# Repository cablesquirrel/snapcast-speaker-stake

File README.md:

# Snapcast Speaker Stake

Hardware and firmware design to retrofit the [Hampton Bay B0029RA](https://www.homedepot.com/p/Hampton-Bay-16-9-in-Black-Outdoor-Landscape-Speaker-B0029RA-2/305754399) outdoor Bluetooth speaker into a [Snapcast](https://github.com/snapcast/snapcast) client.

The design uses an [ESP32-S3 (Seeed XIAO)](https://www.seeedstudio.com/XIAO-ESP32S3-p-5627.html) along with a [I2S DAC](https://www.amazon.com/dp/B08YNJGSN4) and [5-watt amplifier](https://www.amazon.com/dp/B0F6YBYMWY).

## 📁 Repo Layout

```
hardware/
  LICENSE          CERN-OHL-S-2.0
  libraries/       Footprint and symbol libraries used by both boards
  v1/              KiCad project and Gerbers, original 3 W design (MAX98357A)
  v2.0.1/          KiCad project and Gerbers, 5 W design (GY-PCM5102A + CH05D)
firmware/
  snapclient/      Upstream firmware (submodule, pinned to 5cda3a7)
  patches/         upstream-changes.patch: our changes to four upstream files
  overlay/         New files we add (status_led component, speaker-stake sdkconfigs)
  CHANGES.md       Every file and line changed from upstream, with rationale
scripts/
  setup-firmware.ps1  Applies the patch and overlay to firmware/snapclient
releases/
  max98357_combo/  Prebuilt flash images for the 3 W flavor
  pcm5102a_ch05d/  Prebuilt flash images for the 5 W flavor
```

## 💿 Firmware flavors

| Flavor | Hardware | Config | Release |
|---|---|---|---|
| 3 W combo | XIAO + MAX98357A | `firmware/overlay/sdkconfig.max98357_combo` | `releases/max98357_combo/` |
|  | | | |
| 5 W separate | XIAO + GY-PCM5102A + CH05D | `firmware/overlay/sdkconfig.pcm5102a_ch05d` | `releases/pcm5102a_ch05d/` |
|  | | | |

Both flavors are built from the same source tree. They differ only in DAC configuration. See `firmware/CHANGES.md` for the full list of changes from upstream.

## 📦 Flash a prebuilt release

Each release folder contains the four images needed for a full flash:

```
python -m esptool --chip esp32s3 -p COMx write_flash \
  0x0 bootloader.bin 0x8000 partition-table.bin 0x1d000 ota_data_initial.bin 0x20000 snapclient.bin
```

Replace `COMx` with the board's port. Run this from inside the release folder.

## 🛠 Set up ESP-IDF (Windows)

The firmware builds with ESP-IDF **v5.5.1**. Other versions are untested.

1. **Install Git for Windows** from https://git-scm.com/download/win if you don't have it.

2. **Clone ESP-IDF v5.5.1 with submodules.** This takes a while. In PowerShell:
   ```powershell
   mkdir C:\Espressif
   cd C:\Espressif
   git clone -b v5.5.1 --recursive https://github.com/espressif/esp-idf.git
   ```

3. **Install the toolchain for the ESP32-S3:**
   ```powershell
   cd C:\Espressif\esp-idf
   .\install.ps1 esp32s3
   ```
   This downloads the Xtensa compiler, CMake, Ninja, and a Python virtual environment. By default they go under `%USERPROFILE%\.espressif`. To put them elsewhere, set `IDF_TOOLS_PATH` before running the script, for example `$env:IDF_TOOLS_PATH = "C:\Espressif\tools"`.

   If PowerShell blocks the script, run `Set-ExecutionPolicy -Scope CurrentUser RemoteSigned` once and try again.

4. **Activate the environment in every new terminal.** From the `esp-idf` folder:
   ```powershell
   .\export.ps1
   ```
   If you set `IDF_TOOLS_PATH` in step 3, set it again in the terminal first.

5. **Check the install:**
   ```powershell
   idf.py --version
   ```
   It should print `ESP-IDF v5.5.1`.

6. **Connect the board.** The XIAO ESP32-S3 uses its built-in USB-C port, so no USB-serial driver is needed. If no COM port appears, try a different cable. Some cables only charge and don't carry data.

When `idf.py --version` works, continue to **Build from source** below.

## 📚 Build from source

First, clone the repo with its submodules and prepare the firmware. This only needs to be done once per clone:

```powershell
git clone --recursive https://github.com/cablesquirrel/snapcast-speaker-stake
cd snapcast-speaker-stake
.\scripts\setup-firmware.ps1
```

The script checks out upstream at the pinned commit, applies `firmware/patches/upstream-changes.patch`, and copies in the overlay files. It is safe to run again.

Requires ESP-IDF 5.5.1 (see above). Build each flavor from `firmware/snapclient` into its own directory:

```
cd firmware\snapclient
idf.py -B build -D SDKCONFIG=sdkconfig.max98357_combo build
idf.py -B build.pcm5102a_ch05d -D SDKCONFIG=sdkconfig.pcm5102a_ch05d build
```

## 📶 OTA update

With the device on the network, push a new app image to its OTA listener on port 8032. Use a direct file reference so curl sends a Content-Length header:

```
curl <device-ip>:8032 --data-binary @releases/pcm5102a_ch05d/snapclient.bin
```

The connection is reset when the transfer completes. That is expected: the device reboots into the new image.

## 📱 WiFi

WiFi credentials are not compiled in. Provision them over USB-C with Improv WiFi (for example, web.esphome.io).

## 📝 Hardware notes

- Footprint and symbol libraries used by the boards are in `hardware/libraries/`. Each project's `fp-lib-table` and `sym-lib-table` reference them with `${KIPRJMOD}/../libraries/`, so the projects open from a fresh clone. Add the libraries to your global KiCad tables only if you need them outside these projects.
- `hardware/libraries/` contains the Seeed XIAO series, GY-PCM5102A, CH05D (provisional, see its KNOWN_ISSUES), and Adafruit MAX98357A libraries as copied from the local KiCad setup.
- The V2.0.1 known issues are listed in `hardware/v2.0.1/KNOWN_ISSUES.md`. That board was sent to fab with them.

## ⚖ Licensing

- **Hardware** (`hardware/`): [CERN-OHL-S-2.0](hardware/LICENSE), the strongly reciprocal open-source hardware license. The GY-PCM5102A footprint in this project derives from a CERN-OHL-S library, and that license requires derivatives to stay under the same terms.
- **Firmware** (`firmware/`): upstream [CarlosDerSeher/snapclient](https://github.com/CarlosDerSeher/snapclient) is pulled in as a submodule under GPL-3.0 (see `firmware/snapclient/LICENSE`). Our changes are listed in `firmware/CHANGES.md`. Because they modify GPL-3.0 code, they are also GPL-3.0. The firmware overlay files (`status_led` and the sdkconfigs) are included in that same GPL-3.0 grant.
- **Third-party libraries**: the Adafruit MAX98357A library (`adafruit-MAX98357.*`) comes from [besi/kicad-adafruit-MAX98357](https://github.com/besi/kicad-adafruit-MAX98357), and the Seeed XIAO library (`Seeed_Studio_XIAO_Series.*`) comes from Seeed Studio. The Seeed library is CC-BY-SA-4.0 (see `hardware/libraries/LICENSES/`). The Adafruit library has no declared license upstream and is included as-is, pending a takedown request if the owner objects. See `hardware/libraries/README.md`.

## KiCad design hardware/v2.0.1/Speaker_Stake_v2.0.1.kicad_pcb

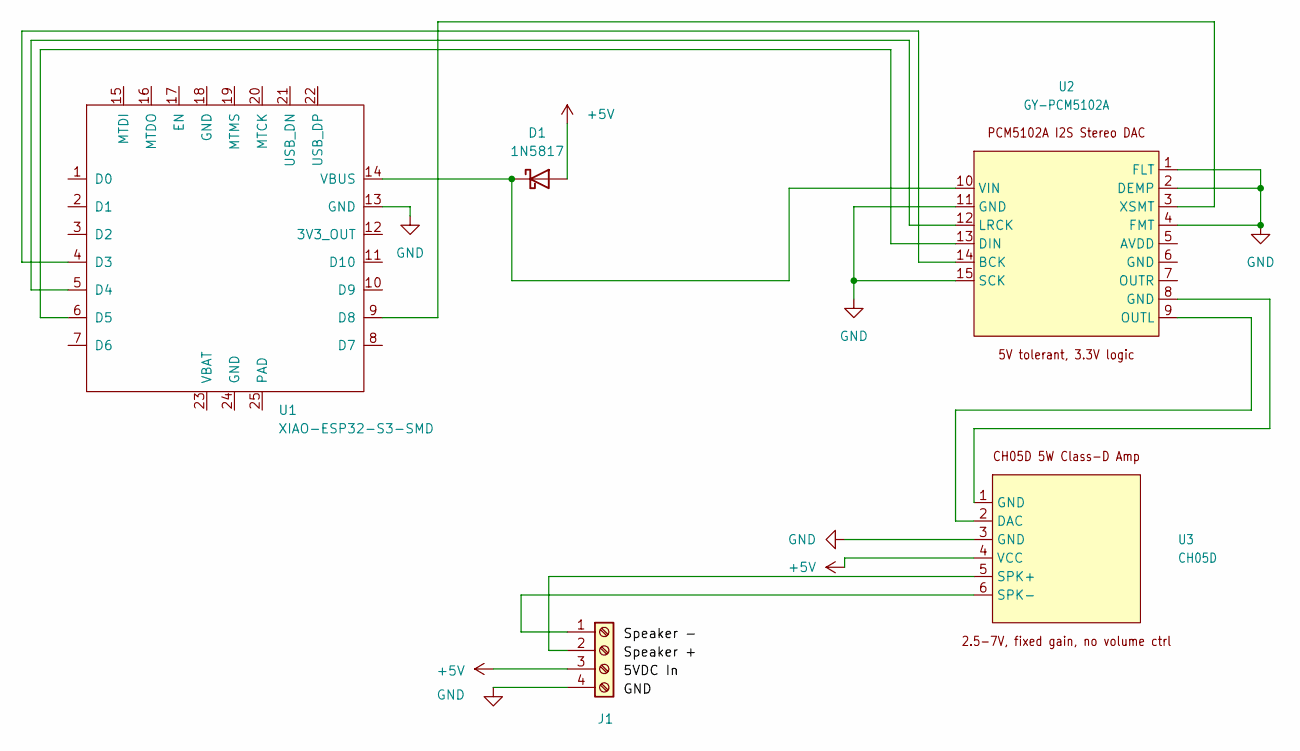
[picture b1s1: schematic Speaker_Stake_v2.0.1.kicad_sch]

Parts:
D1: 1N5817; D_DO-41_SOD81_P10.16mm_Horizontal
J1: Screw_Terminal_01x04; TerminalBlock_Xinya_XY308-2.54-4P_1x04_P2.54mm_Horizontal
U1: XIAO-ESP32-S3-SMD; XIAO-ESP32-S3-DIP
U2: GY-PCM5102A
U3: CH05D

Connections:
+5V: D1.2 (A), J1.3, U3.4 (VCC)
GND: J1.4, U1.13 (GND), U2.1 (FLT), U2.2 (DEMP), U2.4 (FMT), U2.11 (GND), U2.15 (SCK), U3.3 (GND)
unnamed: D1.1 (K), U1.14 (VBUS), U2.10 (VIN)
unnamed: J1.1, U3.6 (SPK-)
unnamed: J1.2, U3.5 (SPK+)
unnamed: U1.4 (D3), U2.14 (BCK)
unnamed: U1.5 (D4), U2.12 (LRCK)
unnamed: U1.6 (D5), U2.13 (DIN)
unnamed: U1.9 (D8), U2.3 (XSMT)
unnamed: U2.8 (GND), U3.1 (GND)
unnamed: U2.9 (OUTL), U3.2 (DAC)

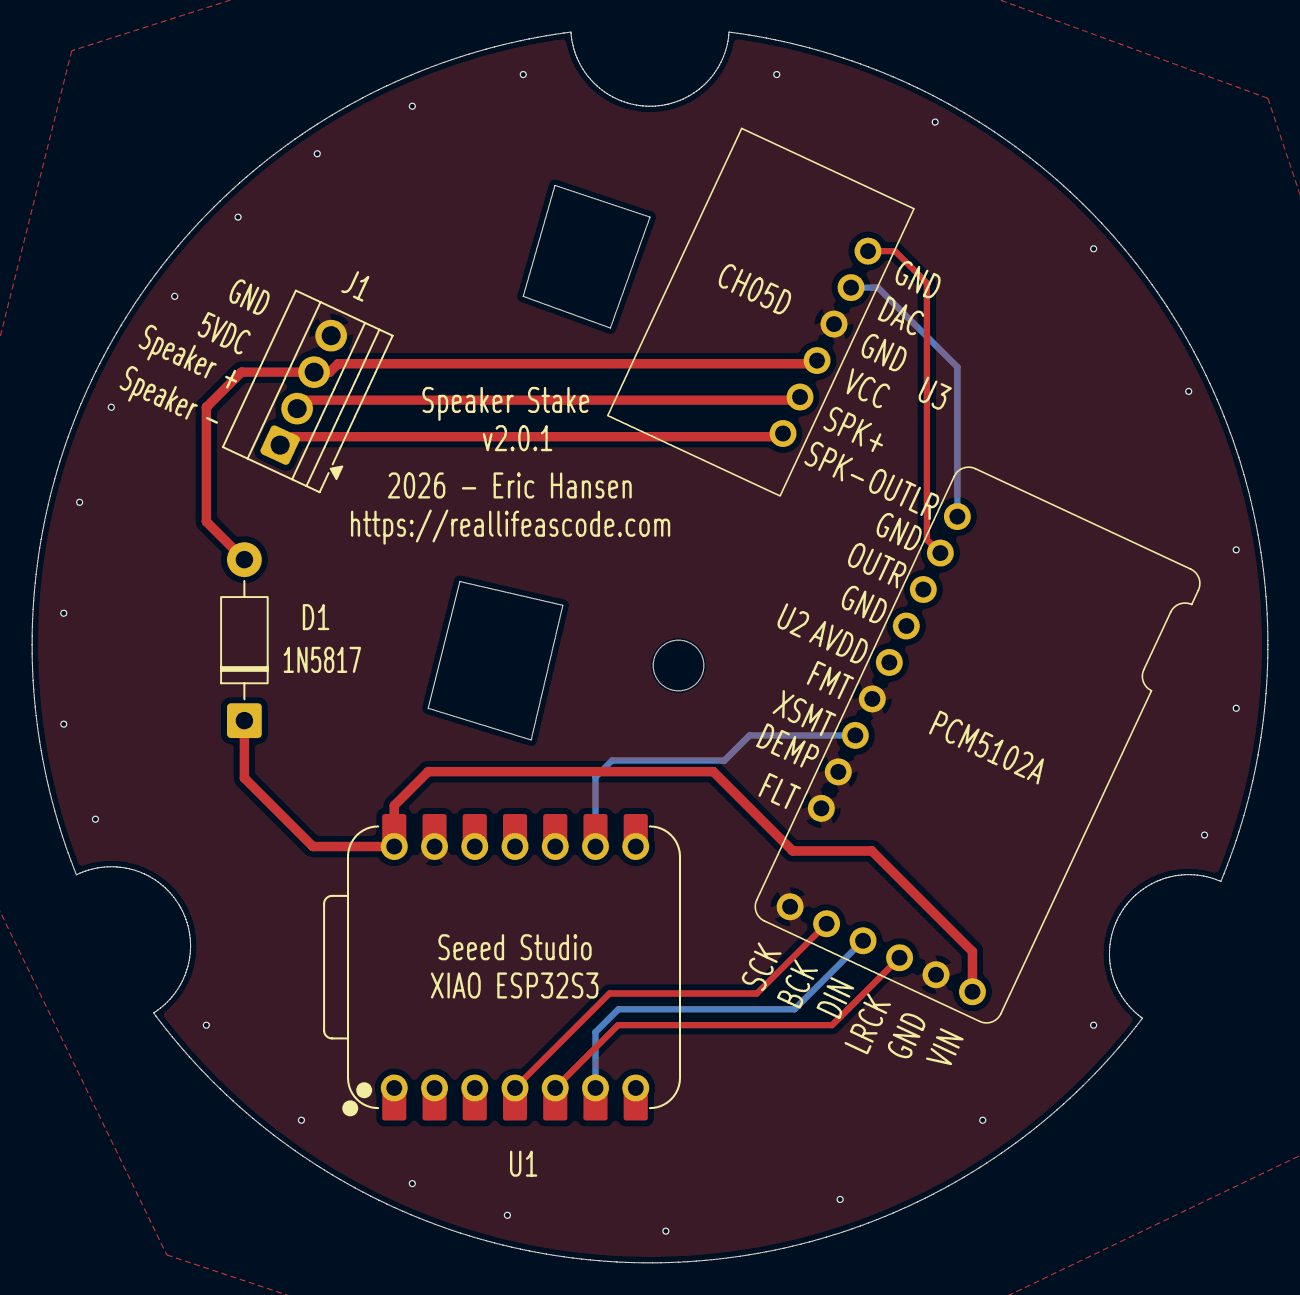
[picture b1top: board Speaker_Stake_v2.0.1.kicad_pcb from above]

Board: 2 copper layers, 78.0 x 77.7 mm, 5 parts (0 on the bottom side), 11 nets.

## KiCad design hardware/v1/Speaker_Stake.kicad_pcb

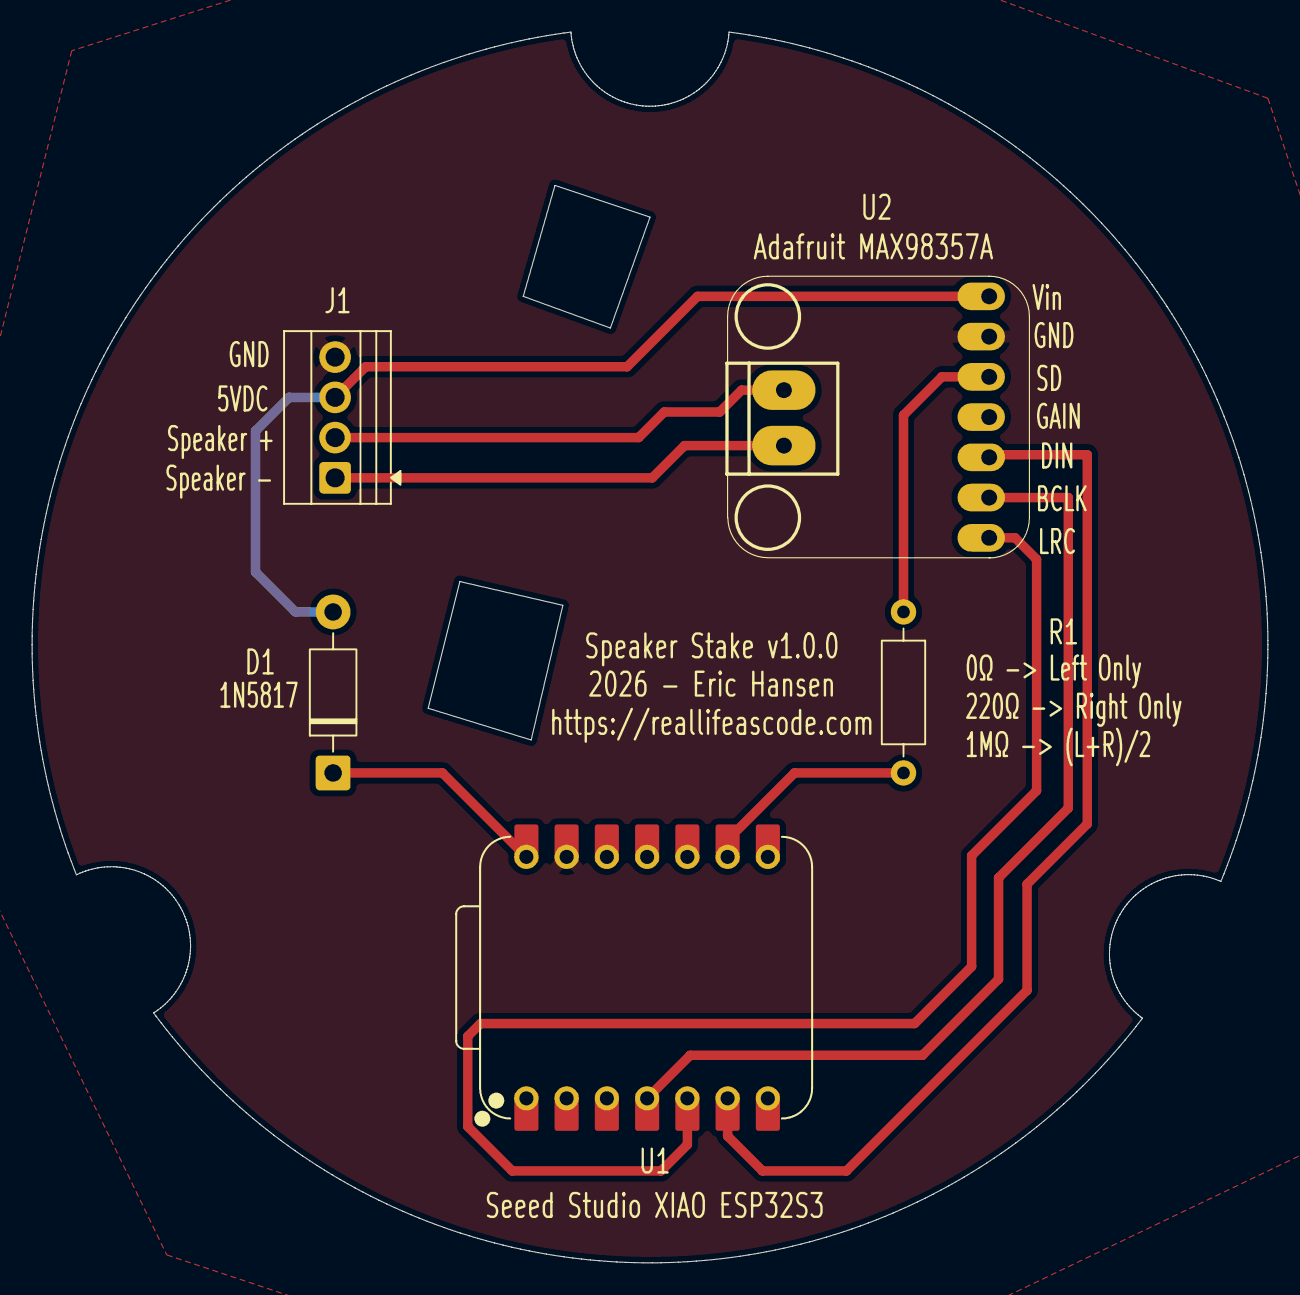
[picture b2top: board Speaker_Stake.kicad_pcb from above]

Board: 2 copper layers, 78.0 x 77.7 mm, 5 parts (0 on the bottom side), 10 nets.

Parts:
D1: 1N5817; D_DO-41_SOD81_P10.16mm_Horizontal
J1: Screw_Terminal_01x04; TerminalBlock_Xinya_XY308-2.54-4P_1x04_P2.54mm_Horizontal
R1: 1M; R_Axial_DIN0207_L6.3mm_D2.5mm_P10.16mm_Horizontal
U1: XIAO-ESP32-S3-SMD; XIAO-ESP32-S3-DIP
U2: adafruit-MAX98357

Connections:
+5V: D1.2 (A), J1.3, U2.1 (Vin)
GND: J1.4, U1.13 (GND), U2.2 (GND)
unnamed: D1.1 (K), U1.14 (VBUS)
unnamed: J1.1, U2.8 (OUTP)
unnamed: J1.2, U2.9 (OUTN)
unnamed: U1.4 (D3), U2.6 (BCLK)
unnamed: U1.5 (D4), U2.7 (LRC)
unnamed: U1.6 (D5), U2.5 (DIN)
unnamed: R1.2, U1.9 (D8)
unnamed: R1.1, U2.3 (~SD_MODE)
